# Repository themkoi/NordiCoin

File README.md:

<h1 align="center">
NordiCoin
</h1>

<p align="center">
Open source BLE tracker with up to 6 years of battery life on a single coin cell.
</p>

- It does not rely on a corporation BLE network to find it. Just you and your devices who track it. Dedicated android app and [watchy](https://github.com/Szybet/InkWatchy) support. The app alerts you once you are out of range
- Design focuses on easy self assembly by individuals
  - Wroom package used to avoid BGA soldering
  - Place for a second MCU in a different package, if the main one is not available. It also exposes all the pins for more features
- Buzzer, to find it easier and a button to stop buzzing
- Wanna use it as a remote for home automation? Sure, that's possible
- Built using the nrf52805
- Firmware written in rust
- Further potential to improve battery life

### Licence
Open Community License v1.1 + General Attribution v1

### Contact
Github issues, [Yatchy discord server](https://github.com/Szybet/Yatchy), [Quill OS matrix space](https://quill-os.org)

### Power consumption
It's a spectrum, the absolute best I got was 3.7uA

But this, at least with the current method is hard to connect to because it's 5s of advertisement delay, not 4s. With 4, it's around 4.5uA. Explore the `battery_life.ods` file to confirm

If someone really wanted to, it would be possible to sync time, advertise only on full minute, make the app do the same and this way it would advertise 15 times less. 10 years of battery life easily achievable. But connecting to it, at least with regular android phones would take long/impossible. That's why I decided the current setup is good enough

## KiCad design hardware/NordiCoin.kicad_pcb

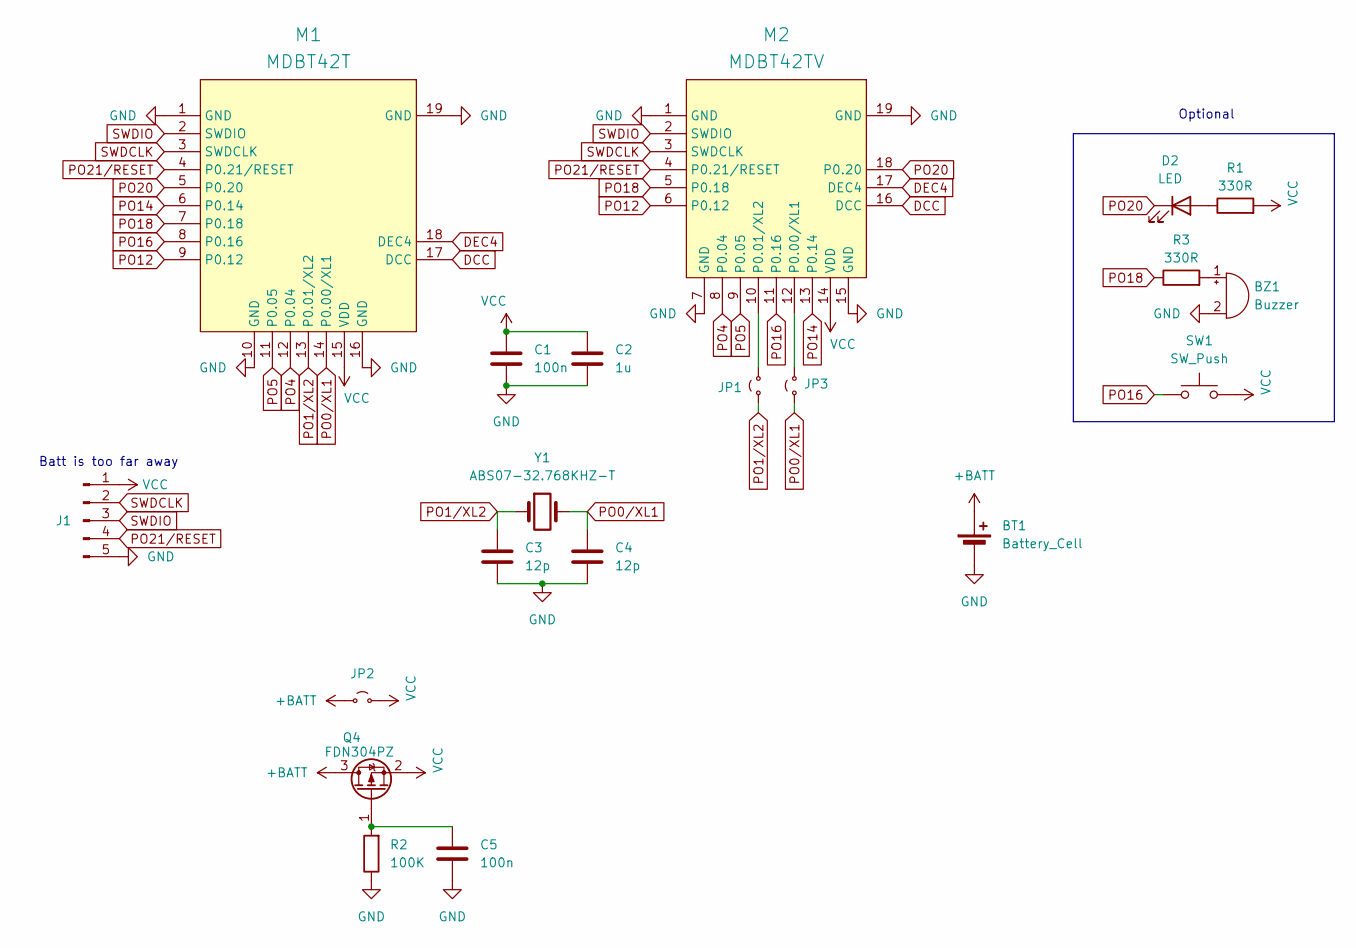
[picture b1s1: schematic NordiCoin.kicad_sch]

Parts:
BT1: Battery_Cell; BAT_120591-1
BZ1: Buzzer; AST0760_MAL
C1, C5: 100n; C_0603_1608Metric
C2: 1u; C_0603_1608Metric
C3, C4: 12p; C_0402_1005Metric
D2: LED; LED_0603_1608Metric
J1: Conn_01x05_Pin; PinHeader_1x05_P1.00mm_Vertical
JP1, JP2, JP3: Jumper_2_Small_Open; SolderJumper_UnBridged_Small
M1: MDBT42T
M2: MDBT42TV
Q4: FDN304PZ; SOT-23
R1, R3: 330R; C_0402_1005Metric
R2: 100K; C_0402_1005Metric
SW1: SW_Push; SW4_PTS815 SJM 250 SMTR LFS_CNK
Y1: ABS07-32.768KHZ-T; XTAL_9HT10_TXC

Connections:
+BATT: BT1.1 (+), JP2.1 (A), Q4.3 (D)
DCC: M1.17 (DCC), M2.16 (DCC)
DEC4: M1.18 (DEC4), M2.17 (DEC4)
GND: BT1.2 (-), BZ1.2 (-), C1.2, C2.2, C3.2, C4.2, C5.2, J1.5, M1.1 (GND), M1.10 (GND), M1.16 (GND), M1.19 (GND), M2.1 (GND), M2.7 (GND), M2.15 (GND), M2.19 (GND), R2.1
unnamed: BZ1.1 (+), R3.2
unnamed: D2.2 (A), R1.1
unnamed: JP1.2 (B), M2.10 (P0.01/XL2)
unnamed: JP3.2 (B), M2.12 (P0.00/XL1)
unnamed: C5.1, Q4.1 (G), R2.2
PO0/XL1: C4.1, JP3.1 (A), M1.14 (P0.00/XL1), Y1.2
PO1/XL2: C3.1, JP1.1 (A), M1.13 (P0.01/XL2), Y1.1
PO4: M1.12 (P0.04), M2.8 (P0.04)
PO5: M1.11 (P0.05), M2.9 (P0.05)
PO12: M1.9 (P0.12), M2.6 (P0.12)
PO14: M1.6 (P0.14), M2.13 (P0.14)
PO16: M1.8 (P0.16), M2.11 (P0.16), SW1.1
PO18: M1.7 (P0.18), M2.5 (P0.18), R3.1
PO20: D2.1 (K), M1.5 (P0.20), M2.18 (P0.20)
PO21/RESET: J1.4, M1.4 (P0.21/RESET), M2.4 (P0.21/RESET)
SWDCLK: J1.2, M1.3 (SWDCLK), M2.3 (SWDCLK)
SWDIO: J1.3, M1.2 (SWDIO), M2.2 (SWDIO)
VCC: C1.1, C2.1, J1.1, JP2.2 (B), M1.15 (VDD), M2.14 (VDD), Q4.2 (S), R1.2, SW1.2

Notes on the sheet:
Batt is too far away
Optional

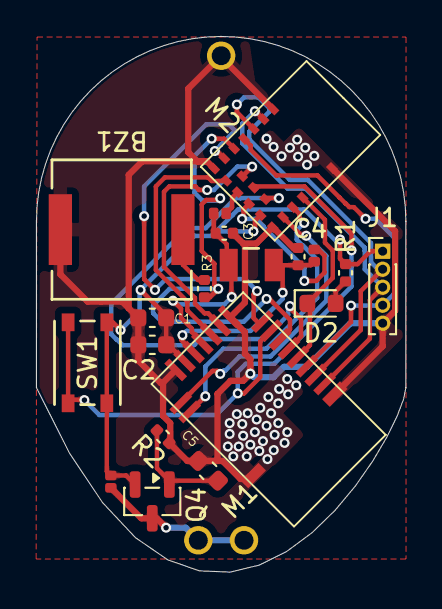
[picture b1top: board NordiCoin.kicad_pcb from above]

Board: 2 copper layers, 20.5 x 29.8 mm, 20 parts (1 on the bottom side), 22 nets.

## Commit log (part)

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2026-02-25 init
2026-02-25 added mcus
2026-02-26 Layout done
2026-02-26 keep out tracks
2026-02-26 done maybe
2026-02-26 done
